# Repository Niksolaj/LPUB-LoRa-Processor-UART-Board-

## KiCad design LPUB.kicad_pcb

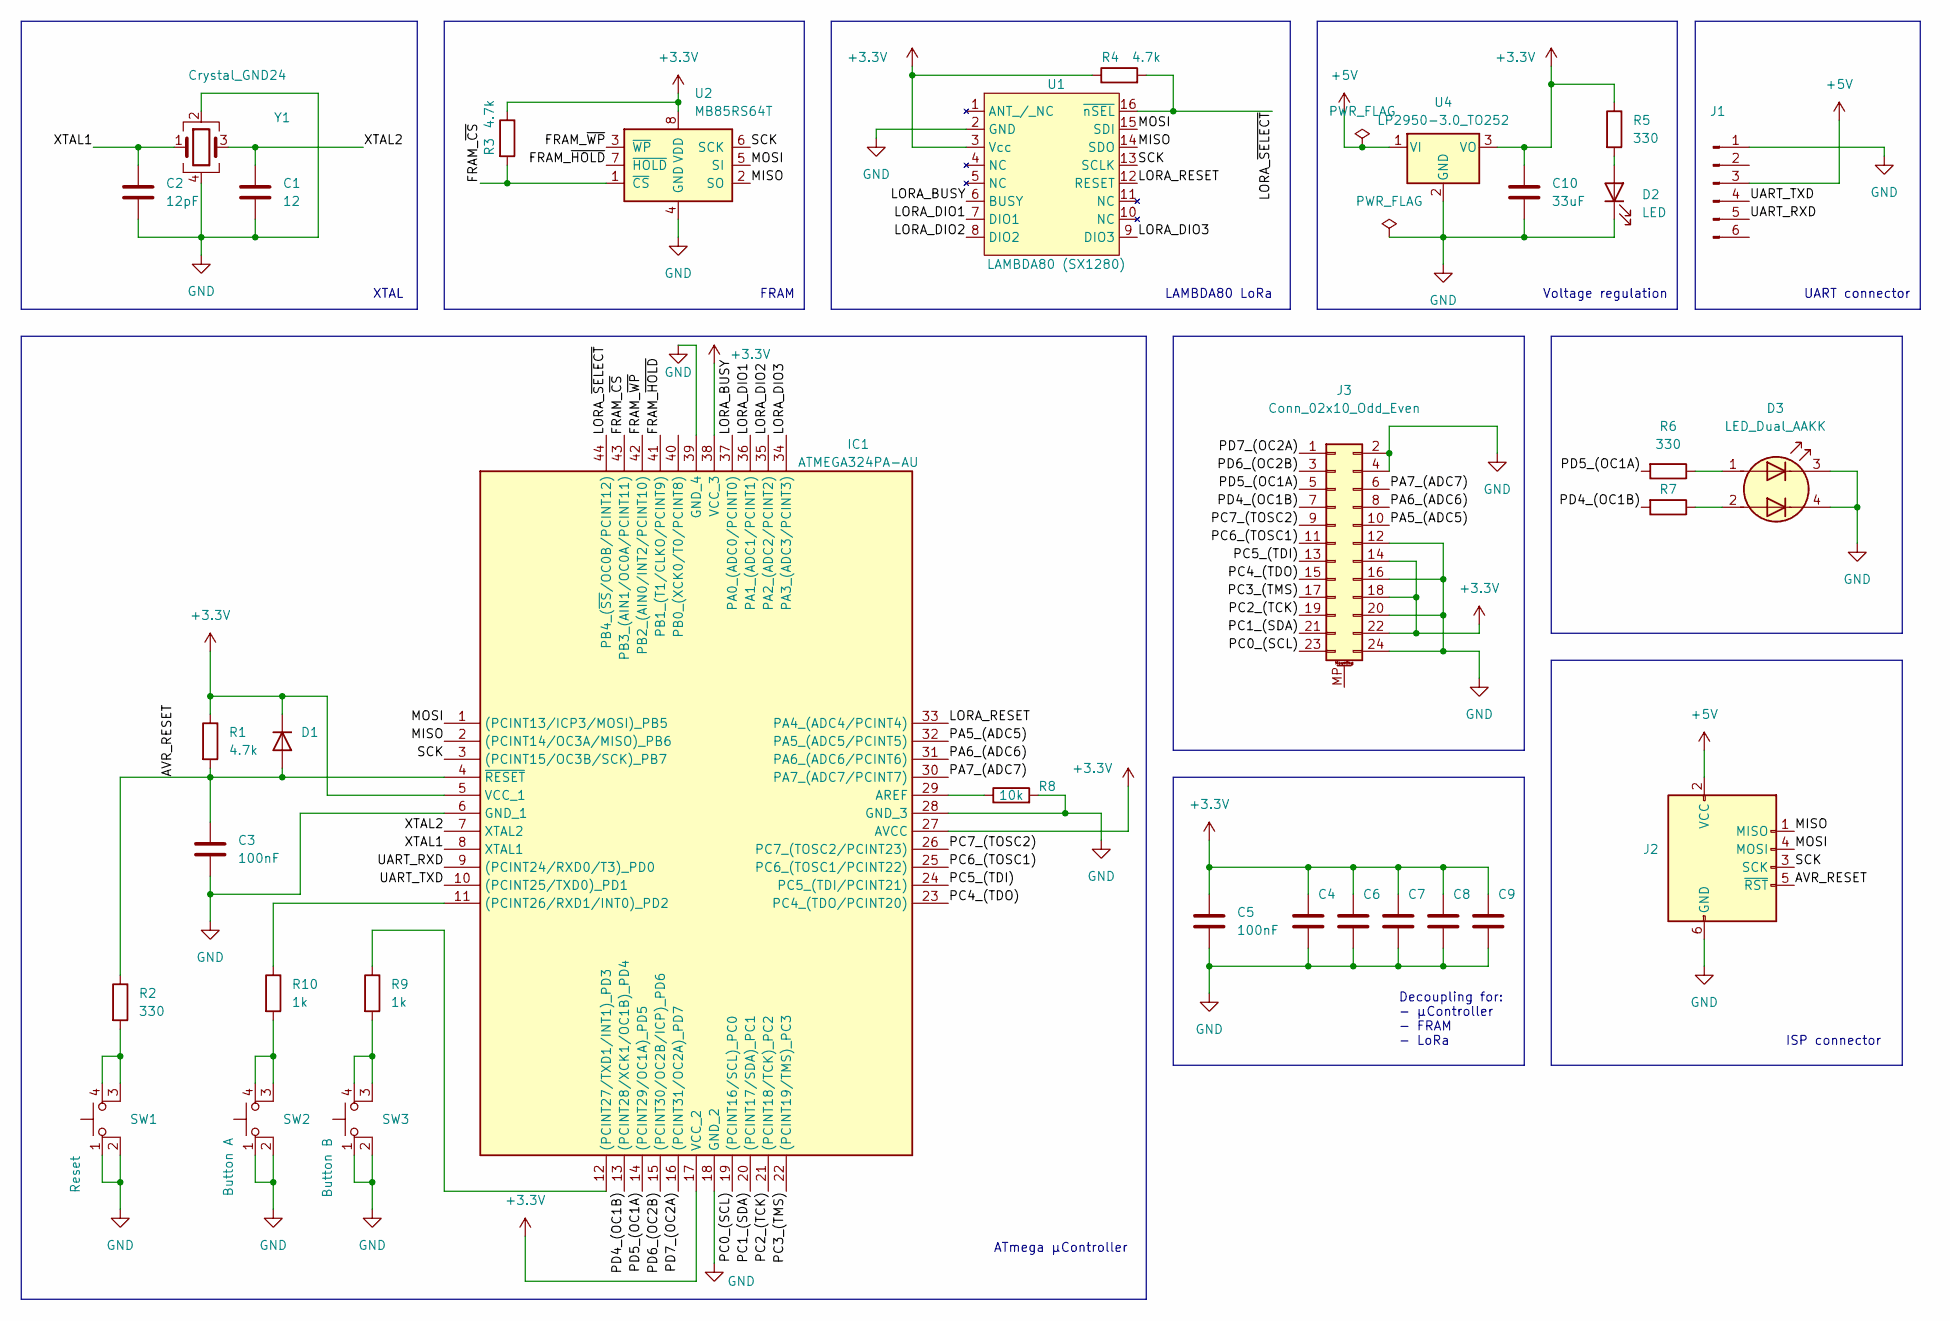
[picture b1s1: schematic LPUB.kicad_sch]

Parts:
C1: 12; C_0805_2012Metric
C2: 12pF; C_0805_2012Metric
C3: 100nF; C_0805_2012Metric_Pad1.18x1.45mm_HandSolder
C4, C5, C6, C7, C8, C9: 100nF; C_0805_2012Metric
C10: 33uF; CP_Elec_8x6.2
D1: D; D_0805_2012Metric_Pad1.15x1.40mm_HandSolder
D2: LED; LED_0805_2012Metric
D3: LED_Dual_AAKK; dual_LED
IC1: ATMEGA324PA-AU; QFP80P1200X1200X120-44N; Mouser2 Part Number 556-ATMEGA324PA-AU
J1: Conn_01x06_Pin; PinHeader_1x06_P2.54mm_Vertical
J2: AVR-ISP-6; AVR_ISP_CON
J3: Conn_02x10_Odd_Even; PinSocket_2x12_P2.54mm_Vertical
R1: 4.7k; R_0805_2012Metric_Pad1.20x1.40mm_HandSolder
R2, R5, R6, R7: 330; R_0805_2012Metric
R3, R4: 4.7k; R_0805_2012Metric
R8: 10k; R_0805_2012Metric
R9, R10: 1k; R_0805_2012Metric
SW1: Reset; SW_Push_1P1T_NO_6x6mm_H9.5mm
SW2: Button A; SW_Push_1P1T_NO_6x6mm_H9.5mm
SW3: Button B; SW_Push_1P1T_NO_6x6mm_H9.5mm
U1: LAMBDA80 (SX1280); LAMBDA80_fp
U2: MB85RS64T; FRAM_fujitsu
U4: LP2950-3.0_TO252; TO-252-2
Y1: Crystal_GND24; Crystal_SMD_2016-4Pin_2.0x1.6mm

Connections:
+3.3V: C4.1, C5.1, C6.1, C7.1, C8.1, C9.1, C10.1, D1.1 (K), IC1.5 (VCC_1), IC1.17 (VCC_2), IC1.27 (AVCC), IC1.38 (VCC_3), J3.14, J3.18, J3.22, R1.1, R3.1, R4.1, R5.1, U1.3 (Vcc), U2.8 (VDD), U4.3 (VO)
+5V: J1.3, J2.2 (VCC), U4.1 (VI)
/AVR_RESET: C3.1, D1.2 (A), IC1.4 (~RESET), J2.5 (~RST), R1.2, R2.1
/FRAM_~CS: IC1.43 (PB3_(AIN1/OC0A/PCINT11)), R3.2, U2.1 (~CS)
/FRAM_~HOLD: IC1.41 (PB1_(T1/CLKO/PCINT9)), U2.7 (~HOLD)
/FRAM_~WP: IC1.42 (PB2_(AIN0/INT2/PCINT10)), U2.3 (~WP)
/LORA_BUSY: IC1.37 (PA0_(ADC0/PCINT0)), U1.6 (BUSY)
/LORA_DIO1: IC1.36 (PA1_(ADC1/PCINT1)), U1.7 (DIO1)
/LORA_DIO2: IC1.35 (PA2_(ADC2/PCINT2)), U1.8 (DIO2)
/LORA_DIO3: IC1.34 (PA3_(ADC3/PCINT3)), U1.9 (DIO3)
/LORA_RESET: IC1.33 (PA4_(ADC4/PCINT4)), U1.12 (RESET)
/LORA_~SELECT: IC1.44 (PB4_(~SS/OC0B/PCINT12)), R4.2, U1.16 (~nSEL)
/MISO: IC1.2 ((PCINT14/OC3A/MISO)_PB6), J2.1 (MISO), U1.14 (SDO), U2.2 (SO)
/MOSI: IC1.1 ((PCINT13/ICP3/MOSI)_PB5), J2.4 (MOSI), U1.15 (SDI), U2.5 (SI)
/PA5_(ADC5): IC1.32 (PA5_(ADC5/PCINT5)), J3.10
/PA6_(ADC6): IC1.31 (PA6_(ADC6/PCINT6)), J3.8
/PA7_(ADC7): IC1.30 (PA7_(ADC7/PCINT7)), J3.6
/PC0_(SCL): IC1.19 ((PCINT16/SCL)_PC0), J3.23
/PC1_(SDA): IC1.20 ((PCINT17/SDA)_PC1), J3.21
/PC2_(TCK): IC1.21 ((PCINT18/TCK)_PC2), J3.19
/PC3_(TMS): IC1.22 ((PCINT19/TMS)_PC3), J3.17
/PC4_(TDO): IC1.23 (PC4_(TDO/PCINT20)), J3.15
/PC5_(TDI): IC1.24 (PC5_(TDI/PCINT21)), J3.13
/PC6_(TOSC1): IC1.25 (PC6_(TOSC1/PCINT22)), J3.11
/PC7_(TOSC2): IC1.26 (PC7_(TOSC2/PCINT23)), J3.9
/PD4_(OC1B): IC1.13 ((PCINT28/XCK1/OC1B)_PD4), J3.7, R7.2
/PD5_(OC1A): IC1.14 ((PCINT29/OC1A)_PD5), J3.5, R6.2
/PD6_(OC2B): IC1.15 ((PCINT30/OC2B/ICP)_PD6), J3.3
/PD7_(OC2A): IC1.16 ((PCINT31/OC2A)_PD7), J3.1
/SCK: IC1.3 ((PCINT15/OC3B/SCK)_PB7), J2.3 (SCK), U1.13 (SCLK), U2.6 (SCK)
/UART_RXD: IC1.9 ((PCINT24/RXD0/T3)_PD0), J1.5
/UART_TXD: IC1.10 ((PCINT25/TXD0)_PD1), J1.4
/XTAL1: C2.2, IC1.8 (XTAL1), Y1.1
/XTAL2: C1.2, IC1.7 (XTAL2), Y1.3
GND: C1.1, C2.1, C3.2, C4.2, C5.2, C6.2, C7.2, C8.2, C9.2, C10.2, D2.1 (K), D3.3 (K1), D3.4 (K2), IC1.6 (GND_1), IC1.18 (GND_2), IC1.28 (GND_3), IC1.39 (GND_4), J1.1, J2.6 (GND), J3.2, J3.4, J3.12, J3.16, J3.20, J3.24, R8.2, SW1.1, SW1.2, SW2.1, SW2.2, SW3.1, SW3.2, U1.2 (GND), U2.4 (GND), U4.2 (GND), Y1.2, Y1.4
unnamed: D2.2 (A), R5.2
unnamed: D3.1 (A1), R6.1
unnamed: D3.2 (A2), R7.1
unnamed: IC1.11 ((PCINT26/RXD1/INT0)_PD2), R10.1
unnamed: IC1.12 ((PCINT27/TXD1/INT1)_PD3), R9.1
unnamed: IC1.29 (AREF), R8.1
unnamed: R2.2, SW1.3 (K), SW1.4 (A)
unnamed: R10.2, SW2.3 (K), SW2.4 (A)
unnamed: R9.2, SW3.3 (K), SW3.4 (A)

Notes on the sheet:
ATmega µController
Decoupling for: - µController - FRAM - LoRa
ISP connector
UART connector
LAMBDA80 LoRa
XTAL
Voltage regulation
FRAM

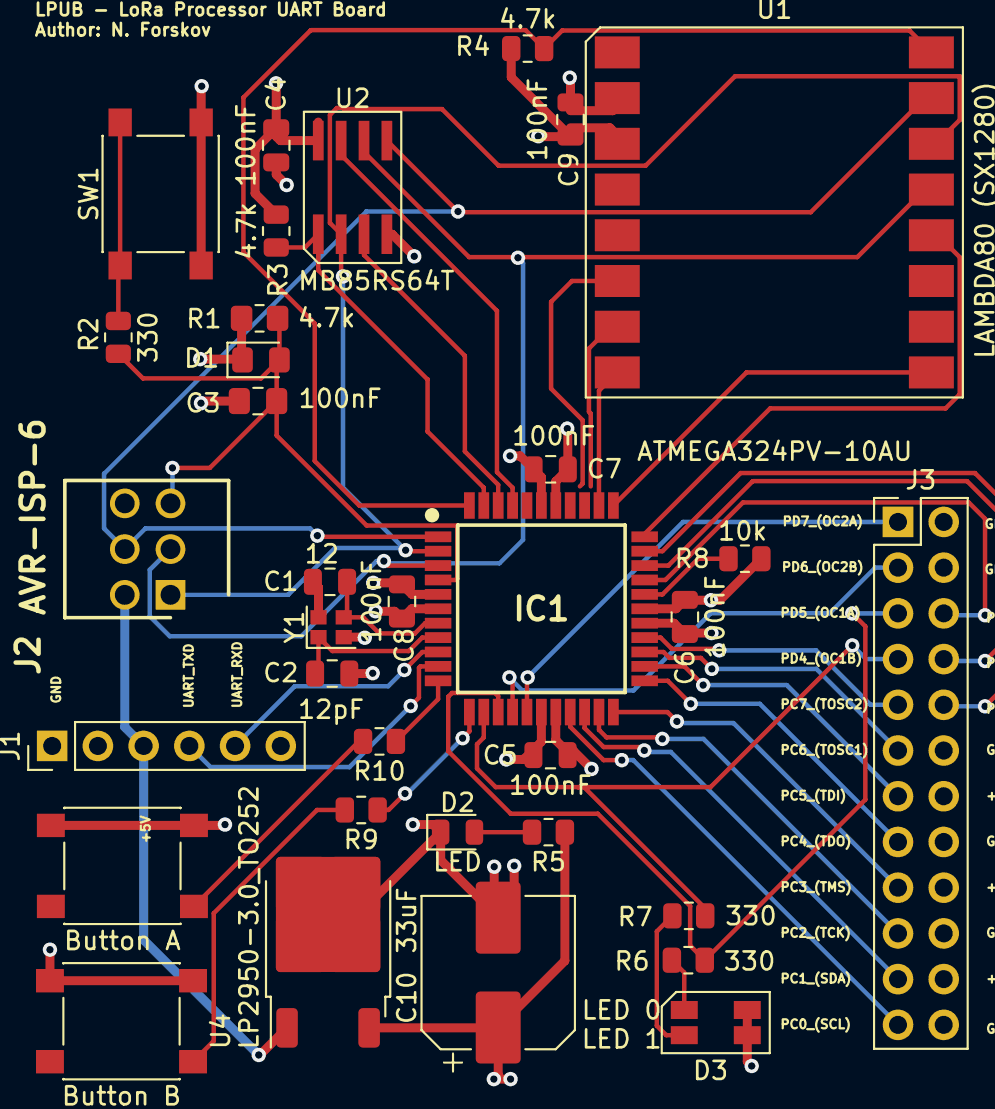
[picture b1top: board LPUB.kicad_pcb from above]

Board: 4 copper layers, 34 parts (0 on the bottom side), 44 nets.

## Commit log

2024-02-27 added Button A and B to schematic
2024-02-27 added and connected Button A and B in PCB
2024-02-28 added gitignore file
2024-02-28 more gitignore and removed files from git
